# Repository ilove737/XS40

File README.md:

# XS40

#### 介绍
80键分体键盘，采用非常便宜的单片机和USB HID接口芯片。目的就是打造一款低成本的机械键盘DIY方案。

hard 文件夹内是键盘的硬件设计文档，PCB设计使用的是KiCad开源软件。

soft 文件夹内是键盘的软件实现。逻辑部分用的是新唐的N76E003单片机。USB接口使用的是 CH9328 USB HID 芯片。

目前的键位设计可以通过  http://www.keyboard-layout-editor.com/#/  站点查看。
打开上述网页点击“Raw data”选项卡，粘贴一下内容即可渲染出键位设计。如有对键位设计有建议的可以在评论区留言，谢谢！
```
[{c:"#6495ed"},"Esc",{c:"#cccccc"},"!\n1","@\n2","#\n3","$\n4","%\n5",{c:"#ff4500"},"~\n`","*",{x:1},"_","+",{c:"#cccccc"},"^\n6","&\n7","*\n8","(\n9",")\n0",{c:"#bb0000"},"Bs"],
[{c:"#444444"},"Tab",{c:"#cccccc"},"Q","W","E","R","T",{c:"#444444"},"{\n[","}\n]",{x:1},"+\n=","|\n\\",{c:"#cccccc"},"Y","U","I","O","P",{c:"#444444"},"del"],
[{c:"#cccccc"},"Caps Lock","A","S","D","F","G","(",{c:"#444444"},")",{x:1},":\n;",{c:"#cccccc"},"<\n,","H","J","K","L","_\n-","Enter"],
[{c:"#ff4500"},"Shift",{c:"#6495ed"},"@",{c:"#cccccc"},"Z","X","C","V","&",{c:"#444444"},"#",{x:1},"\"\n'",{c:"#cccccc"},">\n.","B","N","M","?\n/",{c:"#bb0000"},"↑",{c:"#ff4500"},"RShift"],
[{c:"#6495ed"},"Fn0","Win","Alt",{c:"#ff4500"},"Shift",{c:"#cccccc"},"Space",{c:"#444444"},"Ctrl","~","!",{x:1},"%","?","Ctrl",{c:"#cccccc"},"Space",{c:"#ff4500"},"Fn0",{c:"#bb0000"},"←","↓","→"],

[{y:0.5,c:"#6495ed"},"F0",{c:"#cccccc"},"F1","F2","F3","F4","F5",{c:"#ff4500"},"Num Lock","",{x:1},"","",{c:"#cccccc"},"F6","F7","F8","F9","F10",{c:"#bb0000"},""],
[{c:"#444444"},"select",{c:"#cccccc"},"F11","F12","mail",{a:7},"","",{c:"#444444",a:4},"","",{x:1},"","",{c:"#cccccc"},"7\nHome",{a:4},"8\n↑","|",{a:4},"/","",{c:"#444444"},""],
[{c:"#cccccc"},"prev","play","next","stop",{a:7},"","",{a:4},"",{c:"#444444"},"",{x:1},"",{c:"#cccccc"},"","4\n←",{a:4},"\"",{a:4},":",{a:4},"*","",""],
[{c:"#ff4500",a:4},"vol dn",{c:"#6495ed"},"mute",{c:"#cccccc"},"vol up","app",{a:7},"","",{a:4},"",{c:"#444444"},"",{x:1},"",{c:"#cccccc"},"","1\nEnd","{","}","-",{c:"#bb0000",a:4},"",{c:"#ff4500"},""],
[{c:"#6495ed"},"Fn0","Fn2","Fn4",{c:"#ff4500",a:7},"",{c:"#cccccc"},"",{c:"#444444"},"",{a:4},"","",{x:1},"","","PEnter",{c:"#cccccc"},"0\nIns",{c:"#ff4500"},"Fn0",{c:"#bb0000"},"+","",""]

```

#### 展示

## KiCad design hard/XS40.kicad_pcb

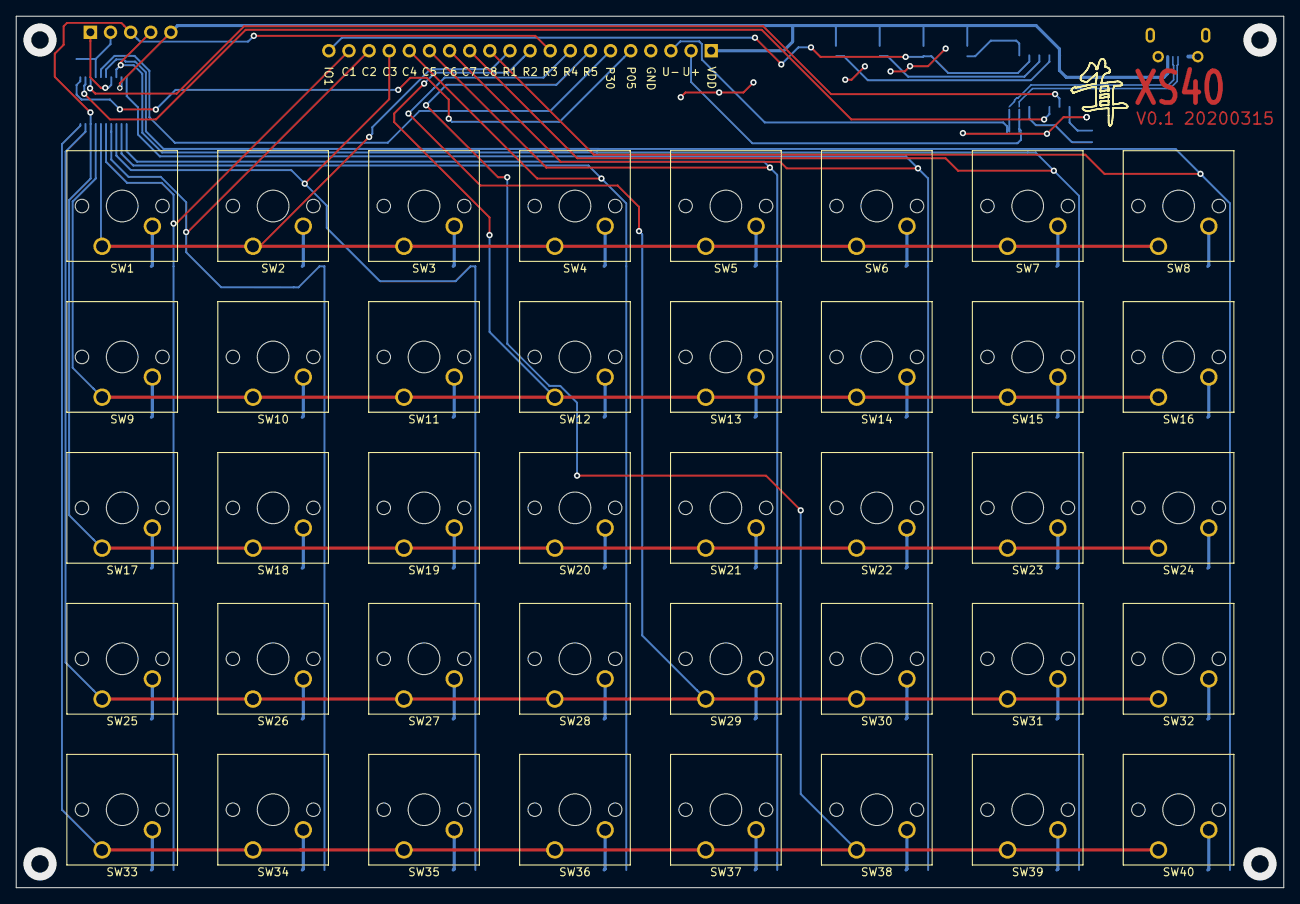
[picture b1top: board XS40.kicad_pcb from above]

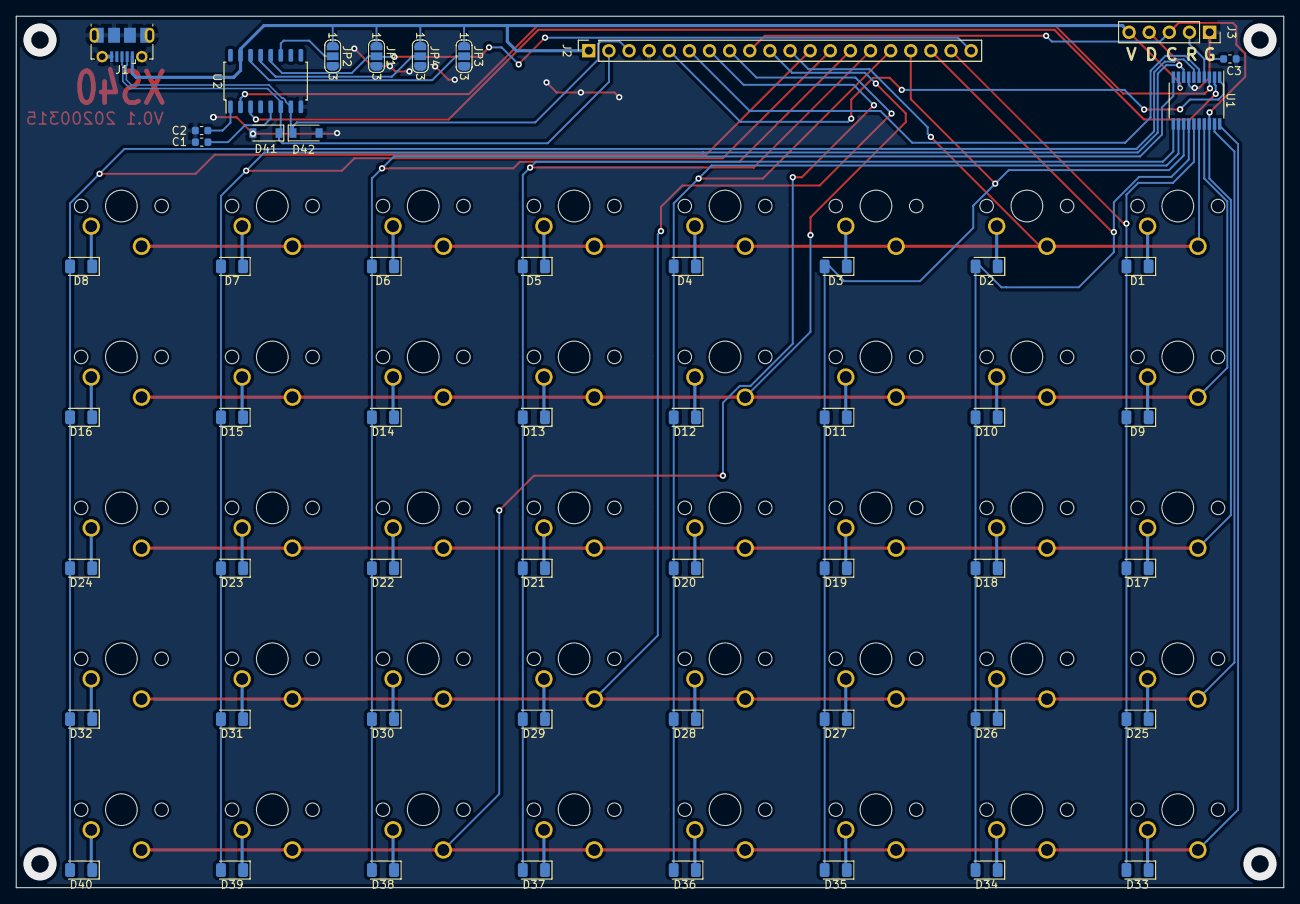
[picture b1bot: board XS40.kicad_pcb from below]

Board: 2 copper layers, 160.0 x 110.0 mm, 94 parts (54 on the bottom side), 68 nets.

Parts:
C1, C3: 0.1uF; C_0603_1608Metric
C2: 200pF; C_0603_1608Metric
D1, D2, D3, D4, D5, D6, D7, D8, D9, D10, D11, D12, D13, D14, D15, D16, D17, D18, D19, D20, D21, D22, D23, D24, D25, D26, D27, D28, D29, D30, D31, D32, D33, D34, D35, D36, D37, D38, D39, D40: D_Small; D_1206_3216Metric
D41, D42: B0520; D_SOD-123
J1: USB_B_Micro; USB_Micro-B_Molex-105017-0001
J2: Conn_01x20_Female; PinSocket_1x20_P2.54mm_Vertical
J3: Nu-link; PinSocket_1x05_P2.54mm_Vertical
JP1, JP2, JP3, JP4: SolderJumper_3_Open; SolderJumper-3_P1.3mm_Open_RoundedPad1.0x1.5mm_NumberLabels
SW1, SW2, SW3, SW4, SW5, SW6, SW7, SW8, SW9, SW10, SW11, SW12, SW13, SW14, SW15, SW16, SW17, SW18, SW19, SW20, SW21, SW22, SW23, SW24, SW25, SW26, SW27, SW28, SW29, SW30, SW31, SW32, SW33, SW34, SW35, SW36, SW37, SW38, SW39, SW40: SW_Push; SW_Cherry_MX_1.00u_PCB
U1: N76E003AT20; TSSOP-20_4.4x6.5mm_P0.65mm
U2: CH9328; SOP-16_4.55x10.3mm_P1.27mm

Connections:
/P05: J2.5, U1.1
/P30: J2.6, U1.5
/RST: C3.2, J3.2, U1.4
COL1: D1.2, D9.2, D17.2, D25.2, D33.2, J2.19, U1.15
COL2: D2.2, D10.2, D18.2, D26.2, D34.2, J2.18, U1.14
COL3: D3.2, D11.2, D19.2, D27.2, D35.2, J2.17, U1.13
COL4: D4.2, D12.2, D20.2, D28.2, D36.2, J2.16, U1.12
COL5: D5.2, D13.2, D21.2, D29.2, D37.2, J2.15, U1.11
COL6: D6.2, D14.2, D22.2, D30.2, D38.2, J2.14, U1.10
COL7: D7.2, D15.2, D23.2, D31.2, D39.2, J2.13, J3.4, U1.8
COL8: D8.2, D16.2, D24.2, D32.2, D40.2, J2.12, U1.6
GND: C1.1, C2.2, C3.1, D41.2, D42.2, J1.5, J1.6, J2.4, J3.1, JP1.3, JP2.3, JP3.3, JP4.3, U1.7, U2.8
IO1: J2.20, JP1.2, U2.12
IO2: JP2.2, U2.11
IO3: JP3.2, U2.14
IO4: JP4.2, U2.13
unnamed: C1.2, U2.5
unnamed: C2.1, U2.1
unnamed: D1.1, SW1.2
unnamed: D2.1, SW2.2
unnamed: D3.1, SW3.2
unnamed: D4.1, SW4.2
unnamed: D5.1, SW5.2
unnamed: D6.1, SW6.2
unnamed: D7.1, SW7.2
unnamed: D8.1, SW8.2
unnamed: D9.1, SW9.2
unnamed: D10.1, SW10.2
unnamed: D11.1, SW11.2
unnamed: D12.1, SW12.2
unnamed: D13.1, SW13.2
unnamed: D14.1, SW14.2
unnamed: D15.1, SW15.2
unnamed: D16.1, SW16.2
unnamed: D17.1, SW17.2
unnamed: D18.1, SW18.2
unnamed: D19.1, SW19.2
unnamed: D20.1, SW20.2
unnamed: D21.1, SW21.2
unnamed: D22.1, SW22.2
unnamed: D23.1, SW23.2
unnamed: D24.1, SW24.2
unnamed: D25.1, SW25.2
unnamed: D26.1, SW26.2
unnamed: D27.1, SW27.2
unnamed: D28.1, SW28.2
unnamed: D29.1, SW29.2
unnamed: D30.1, SW30.2
unnamed: D31.1, SW31.2
unnamed: D32.1, SW32.2
unnamed: D33.1, SW33.2
unnamed: D34.1, SW34.2
unnamed: D35.1, SW35.2
unnamed: D36.1, SW36.2
unnamed: D37.1, SW37.2
unnamed: D38.1, SW38.2
unnamed: D39.1, SW39.2
unnamed: D40.1, SW40.2
ROW1: J2.11, SW1.1, SW2.1, SW3.1, SW4.1, SW5.1, SW6.1, SW7.1, SW8.1, U1.16
ROW2: J2.10, SW9.1, SW10.1, SW11.1, SW12.1, SW13.1, SW14.1, SW15.1, SW16.1, U1.17
ROW3: J2.9, J3.3, SW17.1, SW18.1, SW19.1, SW20.1, SW21.1, SW22.1, SW23.1, SW24.1, U1.18
ROW4: J2.8, SW25.1, SW26.1, SW27.1, SW28.1, SW29.1, SW30.1, SW31.1, SW32.1, U1.19
ROW5: J2.7, SW33.1, SW34.1, SW35.1, SW36.1, SW37.1, SW38.1, SW39.1, SW40.1, U1.20
RXD: U1.3, U2.2
TXD: U1.2, U2.3
UD+: D41.1, J1.3, J2.2, U2.6
UD-: D42.1, J1.2, J2.3, U2.7
VDD: J1.1, J2.1, J3.5, JP1.1, JP2.1, JP3.1, JP4.1, U1.9, U2.15

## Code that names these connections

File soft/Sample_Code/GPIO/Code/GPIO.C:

#include "N76E003.h"
#include "SFR_Macro.h"
#include "Function_define.h"
#include "Common.h"
#include "Delay.h"
#include <string.h>
#include "keyMap.h"

// #define row1 P00
// #define row2 P01
// #define row3 P02
// #define row4 P03
// #define row5 P04

// #define col1 P10
// #define col2 P11
// #define col3 P12
// #define col4 P13
// #define col5 P14
// #define col6 P15
// #define col7 P16
// #define col8 P17

UINT8 xdata i, j;
UINT8 xdata beforeAllKey[5]; // 40个位，保存上一次所有40个建的状态
UINT8 xdata allKey[5];		 // 40个位，保存当前所有40个建的状态

UINT8 xdata kCode;
UINT8 xdata HIDFrames[8];
UINT8 xdata HIDFramesPointer = 2; // 从帧的第三个字节开始添加普通按键的KeyCode

UINT8 xdata Fn0_Status = 0;
UINT8 xdata Fn1_Status = 0;

UINT8 xdata tttt = 0;
UINT16 xdata TH1_INIT = 333;

void makeHIDFrames(void)
{
	Fn0_Status = 0;
	HIDFramesPointer = 2;
	for (i = 0; i < 8; i++)
	{
		HIDFrames[i] = 0;
	}
	if (allKey[0] == 0 && allKey[1] == 0 && allKey[2] == 0 && allKey[3] == 0 && allKey[4] == 0)
	{ // 所有按键都是松开的状态
		for (i = 0; i < 8; i++)
		{
			Send_Data_To_UART0(0x00);
		}
	}
	else
	{ // 有按键按下的状态
		for (i = 0; i < 5; i++)
		{
			if (allKey[i] != 0)
			{
				for (j = 0; j < 8; j++)
				{
					if (allKey[i] >> j & 1)
					{
						if (keyMap[i * 8 + j] == KEY_Fn0)
						{
							Fn0_Status = 1;
						}
						if (keyMap[i * 8 + j] == KEY_Fn1)
						{
							Fn1_Status = 1;
						}
					}
				}
			}
		}

		for (i = 0; i < 5; i++)
		{
			if (allKey[i] != 0)
			{
				for (j = 0; j < 8; j++)
				{
					if (allKey[i] >> j & 1)
					{
						if (Fn0_Status == 1)
						{
							kCode = Fn0_keyMap[i * 8 + j];
						}
						else
						{
							kCode = keyMap[i * 8 + j];
						}
						// if (kCode == KEY_LCTRL | kCode == KEY_LSHIFT | kCode == KEY_LALT | kCode == KEY_LGUI | kCode == KEY_RCTRL | kCode == KEY_RSHIFT | kCode == KEY_RALT | kCode == KEY_RGUI)
						if (kCode >= 0xE0) // Control
						{
							HIDFrames[0] += 0X01 << (kCode & 0X0F);
						}
						else if (kCode >= 0xC0) // 处理shift组合键
						{
							HIDFrames[0] += 0x02;
							HIDFrames[HIDFramesPointer] = kCode - 0xa2;
							HIDFramesPointer++;
						}
						else
						{
							HIDFrames[HIDFramesPointer] = kCode;
							HIDFramesPointer++;
						}
					}
				}
			}
		}
		for (i = 0; i < 8; i++)
		{
			Send_Data_To_UART0(HIDFrames[i]);
		}
	}
}

// 系统时钟      16000 / 16000000 = 0.001s
// 系统时钟1/12  1333  / 1333333  = 0.001s
void Timer1_ISR(void) interrupt 3 //interrupt address is 0x001B
{
	TH1 = (65536 - TH1_INIT) / 256;
	TL1 = (65536 - TH1_INIT) % 256;

	// row1到row5依次拉低
	P0 = 0xFF;
	if (tttt == 5) //所有键扫描完成
	{
		tttt = 0;
		if (memcmp(beforeAllKey, allKey, 5) != 0)
		{
			memcpy(beforeAllKey, allKey, 5);

			makeHIDFrames();
			// Send_Data_To_UART0(allKey[i]);
		}
	}
	else
	{
		if (tttt == 0)
			P00 = 0;
		if (tttt == 1)
			P01 = 0;
		if (tttt == 2)
			P02 = 0;
		if (tttt == 3)
			P03 = 0;
		if (tttt == 4)
			P04 = 0;

		allKey[tttt] = ~P1;

		tttt++;
	}
}

void main(void)
{
	///////////////////////////////////WDT///////////////////////////////////////
	TA = 0xAA;
	TA = 0x55;
	WDCON = 0x07; //Setting WDT prescale
	set_WDTR;	  //WDT run
	set_WDCLR;	  //Clear WDT timer
	set_EWDT;
	EA = 1;
	//set_WIDPD;
	/////////////////////////////////////////////////////////////////////////////

	Set_All_GPIO_Quasi_Mode;

	P00_PushPull_Mode;
	P01_PushPull_Mode;
	P02_PushPull_Mode;
	P03_PushPull_Mode;
	P04_PushPull_Mode;

	TIMER1_MODE1_ENABLE;
	// set_T1M;
	TH1 = (65536 - TH1_INIT) / 256;
	TL1 = (65536 - TH1_INIT) % 256;
	set_ET1; //enable Timer1 interrupt
	set_EA;	 //enable interrupts
	set_TR1; //Timer1 run

	InitialUART0_Timer3(115200);
	// Enable_ADC_AIN1; // Enable AIN0 as ADC input, Find in "Function_define.h" - "ADC INIT"
	// Enable_ADC_AIN7;

	while (1)
	{
		set_WDCLR; // 喂狗
	}
}

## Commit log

2020-03-11 add file
2020-03-11 完成按键扫描逻辑
2020-03-11 add README.md.
2020-03-11 打印出5个字节，包含40个键的状态。
2020-03-12 对比所有按键的前后状态
2020-03-12 删除无用代码
2020-03-12 添加创建帧函数
2020-03-12 add keyScanCode.h
2020-03-12 add keyMap.h
2020-03-13 add usb_hid_keys.h
2020-03-14 添加硬件设计文件
2020-03-14 更新PCB图
2020-03-15 完成生成HID帧方法
2020-03-15 PCB定稿；生成Gerber。
2020-03-21 硬件验证结束，单片机少一根GND线
2020-03-21 定义右边的键位
2020-03-22 PCB添加了少的一根GND线，打包存档v0.1
2020-03-22 修改键位
2020-03-23 添加字体文件
2020-03-25 实现了上档键的复合键；更新了键位布局。
2020-03-29 规划Fn层键位
2020-04-06 新加STM32的实现
2020-04-14 添加了Fn键的功能；修改了部分键位排布。
2020-04-30 删除STM32软件
2020-05-01 readme
2020-05-01 删除文件 .vscode
2020-05-01 add LICENSE.
2020-05-01 添加图片
2020-05-01 update README.md.
